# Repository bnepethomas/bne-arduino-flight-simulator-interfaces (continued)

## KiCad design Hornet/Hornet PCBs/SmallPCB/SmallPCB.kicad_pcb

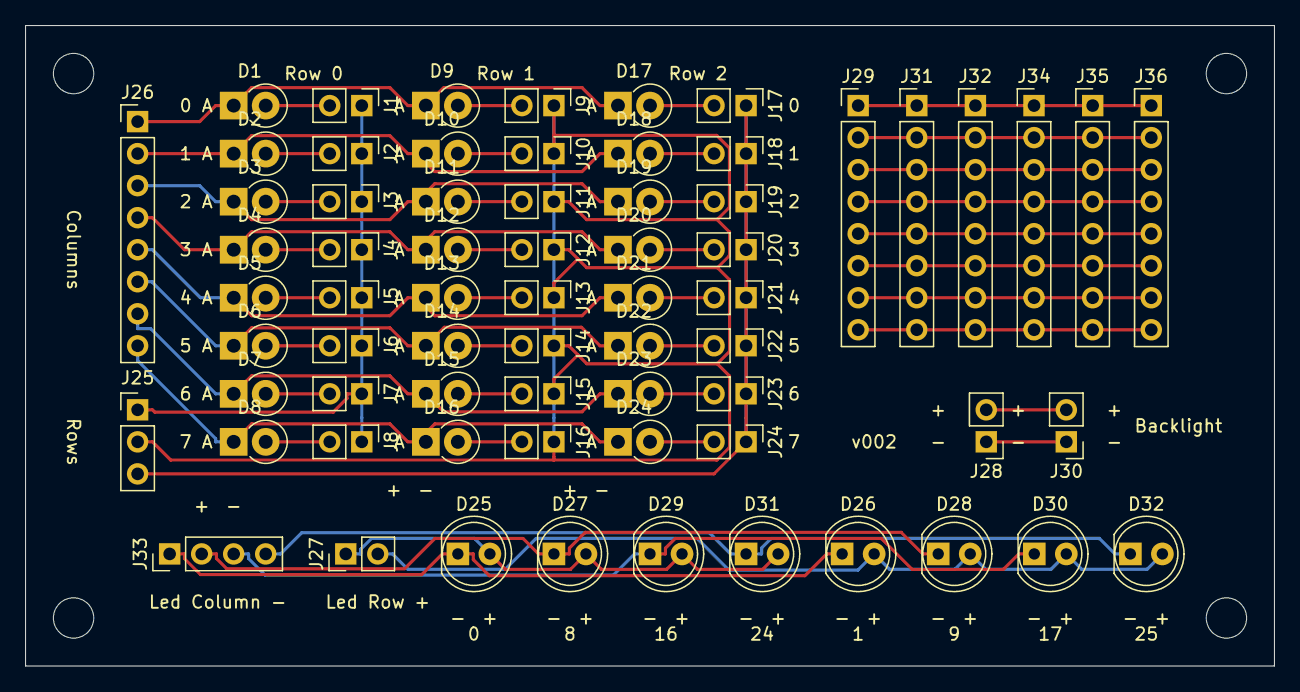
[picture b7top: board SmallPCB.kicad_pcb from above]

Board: 2 copper layers, 99.1 x 50.8 mm, 72 parts (0 on the bottom side), 51 nets.

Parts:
D1, D2, D3, D4, D5, D6, D7, D8, D9, D10, D11, D12, D13, D14, D15, D16, D17, D18, D19, D20, D21, D22, D23, D24: DIODE; D_DO-41_SOD81_P2.54mm_Vertical_KathodeUp
D25, D26, D27, D28, D29, D30, D31, D32: LD271; LED_D5.0mm_IRGrey
J1, J2, J3, J4, J5, J6, J7, J8, J9, J10, J11, J12, J13, J14, J15, J16, J17, J18, J19, J20, J21, J22, J23, J24, J28, J30: Conn_01x02_Male; PinHeader_1x02_P2.54mm_Vertical
J25: Conn_01x11; PinHeader_1x03_P2.54mm_Vertical
J26: Conn_01x16_Female; PinHeader_1x08_P2.54mm_Vertical
J27: Conn_01x04_Female; PinHeader_1x02_P2.54mm_Vertical
J29, J31, J32, J34, J35, J36: Conn_01x08_Female; PinHeader_1x08_P2.54mm_Vertical
J33: Conn_01x04_Female; PinHeader_1x04_P2.54mm_Vertical
MH1, MH2, MH3, MH4: MountingHole_3.2mm_M3

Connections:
/Col0: J1.1, J2.1, J3.1, J4.1, J5.1, J6.1, J7.1, J8.1, J25.1
/Col1: J9.1, J10.1, J11.1, J12.1, J13.1, J14.1, J15.1, J16.1, J25.2
/Col2: J17.1, J18.1, J19.1, J20.1, J21.1, J22.1, J23.1, J24.1, J25.3
/Row0: D1.1, D9.1, D17.1, J26.1
/Row1: D2.1, D10.1, D18.1, J26.2
/Row2: D3.1, D11.1, D19.1, J26.3
/Row3: D4.1, D12.1, D20.1, J26.4
/Row4: D5.1, D13.1, D21.1, J26.5
/Row5: D6.1, D14.1, D22.1, J26.6
/Row6: D7.1, D15.1, D23.1, J26.7
/Row7: D8.1, D16.1, D24.1, J26.8
/Spare0: J29.1, J31.1, J32.1, J34.1, J35.1, J36.1
/Spare1: J29.2, J31.2, J32.2, J34.2, J35.2, J36.2
/Spare2: J29.3, J31.3, J32.3, J34.3, J35.3, J36.3
/Spare3: J29.4, J31.4, J32.4, J34.4, J35.4, J36.4
/Spare4: J29.5, J31.5, J32.5, J34.5, J35.5, J36.5
/Spare5: J29.6, J31.6, J32.6, J34.6, J35.6, J36.6
/Spare6: J29.7, J31.7, J32.7, J34.7, J35.7, J36.7
/Spare7: J29.8, J31.8, J32.8, J34.8, J35.8, J36.8
unnamed: D1.2, J1.2
unnamed: D2.2, J2.2
unnamed: D3.2, J3.2
unnamed: D4.2, J4.2
unnamed: D5.2, J5.2
unnamed: D6.2, J6.2
unnamed: D7.2, J7.2
unnamed: D8.2, J8.2
unnamed: D9.2, J9.2
unnamed: D10.2, J10.2
unnamed: D11.2, J11.2
unnamed: D12.2, J12.2
unnamed: D13.2, J13.2
unnamed: D14.2, J14.2
unnamed: D15.2, J15.2
unnamed: D16.2, J16.2
unnamed: D17.2, J17.2
unnamed: D18.2, J18.2
unnamed: D19.2, J19.2
unnamed: D20.2, J20.2
unnamed: D21.2, J21.2
unnamed: D22.2, J22.2
unnamed: D23.2, J23.2
unnamed: D24.2, J24.2
unnamed: D25.1, D26.1, J33.1
unnamed: D25.2, D27.2, D29.2, D31.2, J27.1
unnamed: D26.2, D28.2, D30.2, D32.2, J27.2
unnamed: D27.1, D28.1, J33.2
unnamed: D29.1, D30.1, J33.3
unnamed: D31.1, D32.1, J33.4
unnamed: J28.1, J30.1
unnamed: J28.2, J30.2

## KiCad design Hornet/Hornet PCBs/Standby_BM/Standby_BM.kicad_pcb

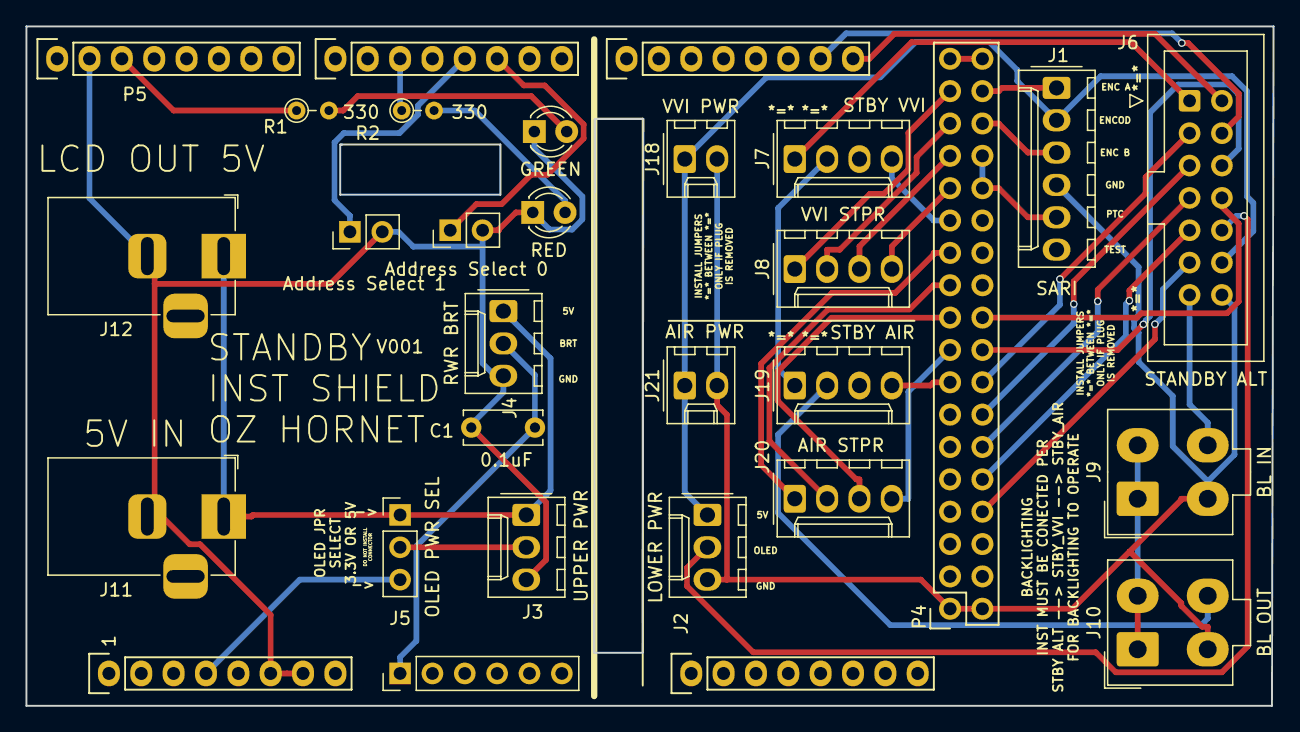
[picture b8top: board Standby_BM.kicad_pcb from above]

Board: 2 copper layers, 97.9 x 53.3 mm, 30 parts (0 on the bottom side), 42 nets.

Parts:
C1: 0.1uF; C_Disc_D6.0mm_W2.5mm_P5.00mm
D1: GREEN; LED_D3.0mm
D2: RED; LED_D3.0mm
J1: SARI; Molex_KK-254_AE-6410-06A_1x06_P2.54mm_Vertical
J2: LOWER PWR; Molex_KK-254_AE-6410-03A_1x03_P2.54mm_Vertical
J3: UPPER PWR; Molex_KK-254_AE-6410-03A_1x03_P2.54mm_Vertical
J4: RWR BRT; Molex_KK-254_AE-6410-03A_1x03_P2.54mm_Vertical
J5: OLED PWR SEL; PinHeader_1x03_P2.54mm_Vertical
J6: STANDBY ALT; IDC-Header_2x07_P2.54mm_Vertical
J7: STBY VVI; Molex_KK-254_AE-6410-04A_1x04_P2.54mm_Vertical
J8: VVI STPR; Molex_KK-254_AE-6410-04A_1x04_P2.54mm_Vertical
J9: BL IN; Molex_Mini-Fit_Jr_5566-04A_2x02_P4.20mm_Vertical
J10: BL OUT; Molex_Mini-Fit_Jr_5566-04A_2x02_P4.20mm_Vertical
J11: 5V IN; BarrelJack_Horizontal
J12: LCD OUT 5V; BarrelJack_Horizontal
J16: Address Select 0; PinHeader_1x02_P2.54mm_Vertical
J17: Address Select 1; PinHeader_1x02_P2.54mm_Vertical
J18: VVI PWR; Molex_KK-254_AE-6410-02A_1x02_P2.54mm_Vertical
J19: STBY AIR; Molex_KK-254_AE-6410-04A_1x04_P2.54mm_Vertical
J20: AIR STPR; Molex_KK-254_AE-6410-04A_1x04_P2.54mm_Vertical
J21: AIR PWR; Molex_KK-254_AE-6410-02A_1x02_P2.54mm_Vertical
P1: Power; Socket_Strip_Arduino_1x08
P2: Analog; PinHeader_1x06_P2.54mm_Vertical
P3: Analog; Socket_Strip_Arduino_1x08
P4: Digital; Socket_Strip_Arduino_2x18
P5, P6: PWM; Socket_Strip_Arduino_1x08
P7: Communication; Socket_Strip_Arduino_1x08
R1, R2: 330; PT_R_Axial_DIN0204_L3.6mm_D1.6mm_P2.54mm_Vertical

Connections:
+3V3: J5.3, P1.4
+5V: P4.35, P4.36
/21(SCL): J6.2, P7.8
/22: J8.1, P4.33
/23: J1.1, P4.34
/24: J8.2, P4.31
/25: J1.3, P4.32
/26: J8.3, P4.29
/28: J8.4, P4.27
/30: J7.4, P4.25
/32: J20.1, P4.23
/34: J20.2, P4.21
/36: J20.3, P4.19
/37: J6.8, P4.20
/38: J20.4, P4.17
/39: J6.6, P4.18
/40: J19.4, P4.15
/41: J6.3, P4.16
/43: J6.5, P4.14
/45: J6.7, P4.12
/47: J6.9, P4.10
/49: J6.11, P4.8
/A0: C1.1, J4.2, P2.1
/ADDRESS_SELECT_0: J16.1, P6.6
/ADDRESS_SELECT_1: J17.1, P6.5
/AIR_LED_OUT: J10.4, J19.2
/ALT_LED_IN: J6.13, J9.4
/ALT_LED_OUT-VVI_LED_IN: J6.1, J7.1
/D5: P6.3, R2.1
/D13: P5.3, R1.1
/LED+5V: J9.1, J9.2, J10.1, J10.2
/LOWER_OUTPUT_5V: J1.2, J2.1, J6.12, J18.1, J21.1
/OLED_PWR(L): J2.2, J6.10
/OLED_PWR(U): J3.2, J5.2
/SARI_SW: J1.5, P4.28, P4.30
/SDA: J6.4, P7.7
/UPPER_OUTPUT_5V: J3.1, J4.1, J5.1, J11.1, J12.1
/VVI_LED_OUT-AIR_LED_IN: J7.2, J19.1
GND: J1.4, J2.3, J6.14, J9.3, J10.3, J18.2, J21.2, P4.1, P4.2
GNDD: C1.2, D1.1 (K), D2.1 (K), J3.3, J4.3, J11.2, J12.2, J16.2, J17.2, P1.6, P1.7, P5.2
unnamed: D1.2 (A), R1.2
unnamed: D2.2 (A), R2.2
